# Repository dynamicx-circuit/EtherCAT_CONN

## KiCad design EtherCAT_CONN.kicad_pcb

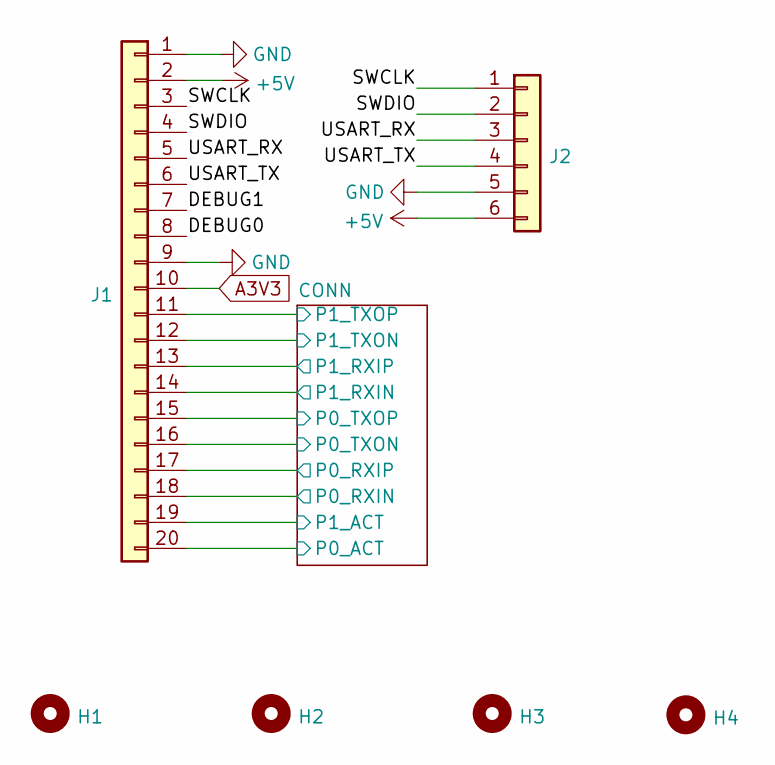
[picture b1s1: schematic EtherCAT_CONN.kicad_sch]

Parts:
H1, H2, H3, H4: MountingHole; M1.6
J1: Conn_01x20; ECAT_20pin
J2: Conn_01x06; JST_SH_BM06B-SRSS-TB_1x06-1MP_P1.00mm_Vertical

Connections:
+5V: J1.2, J2.6
/CONN/P0_ACT: J1.20; also elsewhere on the board
/CONN/P0_RXIN: J1.18; also elsewhere on the board
/CONN/P0_RXIP: J1.17; also elsewhere on the board
/CONN/P0_TXON: J1.16; also elsewhere on the board
/CONN/P0_TXOP: J1.15; also elsewhere on the board
/CONN/P1_ACT: J1.19; also elsewhere on the board
/CONN/P1_RXIN: J1.14; also elsewhere on the board
/CONN/P1_RXIP: J1.13; also elsewhere on the board
/CONN/P1_TXON: J1.12; also elsewhere on the board
/CONN/P1_TXOP: J1.11; also elsewhere on the board
/DEBUG0: J1.8
/DEBUG1: J1.7
/SWCLK: J1.3, J2.1
/SWDIO: J1.4, J2.2
/USART_RX: J1.5, J2.3
/USART_TX: J1.6, J2.4
A3V3: J1.10; also elsewhere on the board
GND: J1.1, J1.9, J2.5; also elsewhere on the board

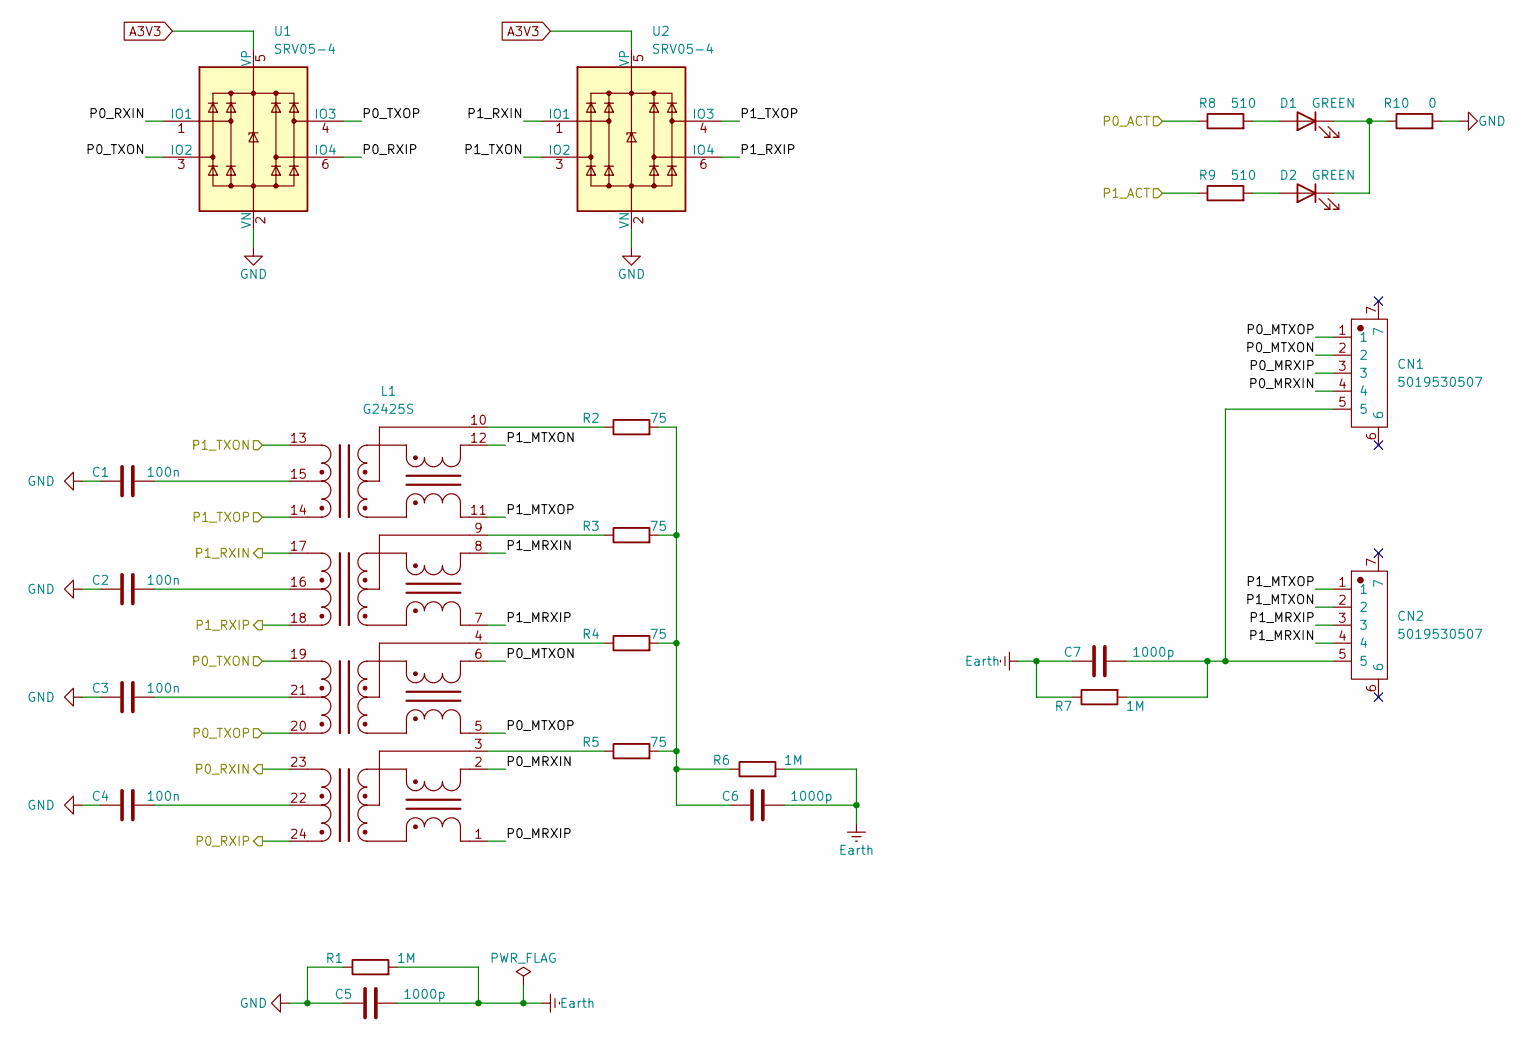
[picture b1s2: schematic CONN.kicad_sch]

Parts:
C1, C2, C3, C4: 100n; C_0603_1608Metric
C5, C6, C7: 1000p; C_1206_3216Metric
CN1, CN2: 5019530507; CONN-TH_5019530507
D1, D2: GREEN; LED_0603_1608Metric
L1: G2425S; SMD-24_L16.5-W9.0-P1.27-LS9.7-BL
R1, R6, R7: 1M; R_1206_3216Metric
R2, R3, R4, R5: 75; R_0603_1608Metric
R8, R9: 510; R_0603_1608Metric
R10: 0; R_0603_1608Metric
U1, U2: SRV05-4; SOT-23-6

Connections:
/CONN/P0_ACT: R8.1; also elsewhere on the board
/CONN/P0_MRXIN: CN1.4, L1.2
/CONN/P0_MRXIP: CN1.3, L1.1
/CONN/P0_MTXON: CN1.2, L1.6
/CONN/P0_MTXOP: CN1.1, L1.5
/CONN/P0_RXIN: L1.23, U1.1 (IO1); also elsewhere on the board
/CONN/P0_RXIP: L1.24, U1.6 (IO4); also elsewhere on the board
/CONN/P0_TXON: L1.19, U1.3 (IO2); also elsewhere on the board
/CONN/P0_TXOP: L1.20, U1.4 (IO3); also elsewhere on the board
/CONN/P1_ACT: R9.1; also elsewhere on the board
/CONN/P1_MRXIN: CN2.4, L1.8
/CONN/P1_MRXIP: CN2.3, L1.7
/CONN/P1_MTXON: CN2.2, L1.12
/CONN/P1_MTXOP: CN2.1, L1.11
/CONN/P1_RXIN: L1.17, U2.1 (IO1); also elsewhere on the board
/CONN/P1_RXIP: L1.18, U2.6 (IO4); also elsewhere on the board
/CONN/P1_TXON: L1.13, U2.3 (IO2); also elsewhere on the board
/CONN/P1_TXOP: L1.14, U2.4 (IO3); also elsewhere on the board
A3V3: U1.5 (VP), U2.5 (VP); also elsewhere on the board
Earth: C5.2, C6.2, C7.1, R1.2, R6.2, R7.1
GND: C1.1, C2.1, C3.1, C4.1, C5.1, R1.1, R10.2, U1.2 (VN), U2.2 (VN); also elsewhere on the board
unnamed: C1.2, L1.15
unnamed: C2.2, L1.16
unnamed: C3.2, L1.21
unnamed: C4.2, L1.22
unnamed: C6.1, R2.2, R3.2, R4.2, R5.2, R6.1
unnamed: C7.2, CN1.5, CN2.5, R7.2
unnamed: D1.2 (A), R8.2
unnamed: D1.1 (K), D2.1 (K), R10.1
unnamed: D2.2 (A), R9.2
unnamed: L1.3, R5.1
unnamed: L1.4, R4.1
unnamed: L1.9, R3.1
unnamed: L1.10, R2.1

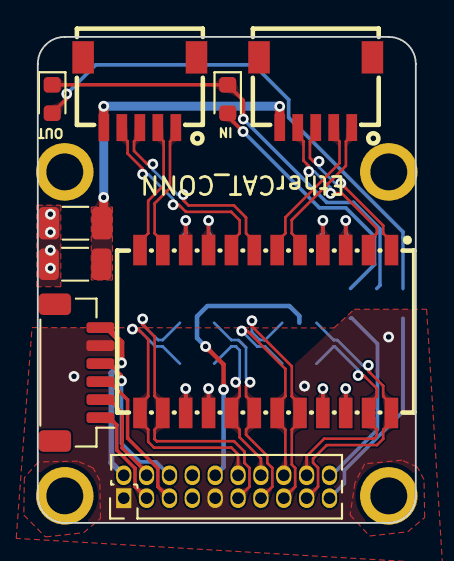
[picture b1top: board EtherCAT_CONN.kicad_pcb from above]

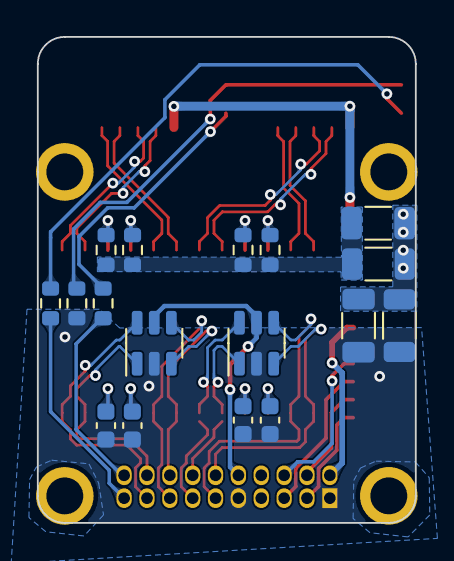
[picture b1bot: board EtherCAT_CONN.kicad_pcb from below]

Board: 2 copper layers, 21.0 x 27.0 mm, 30 parts (17 on the bottom side), 39 nets.

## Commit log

2023-06-29 Change routings
2023-07-08 All 0603 version
2023-07-14 Official version
2023-07-19 Fixed LED_IN and LED_OUT bug
